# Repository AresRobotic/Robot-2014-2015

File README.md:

Robot-2014-2015
===============

Tous les documents, codes et cartes du robot de la coupe 2015

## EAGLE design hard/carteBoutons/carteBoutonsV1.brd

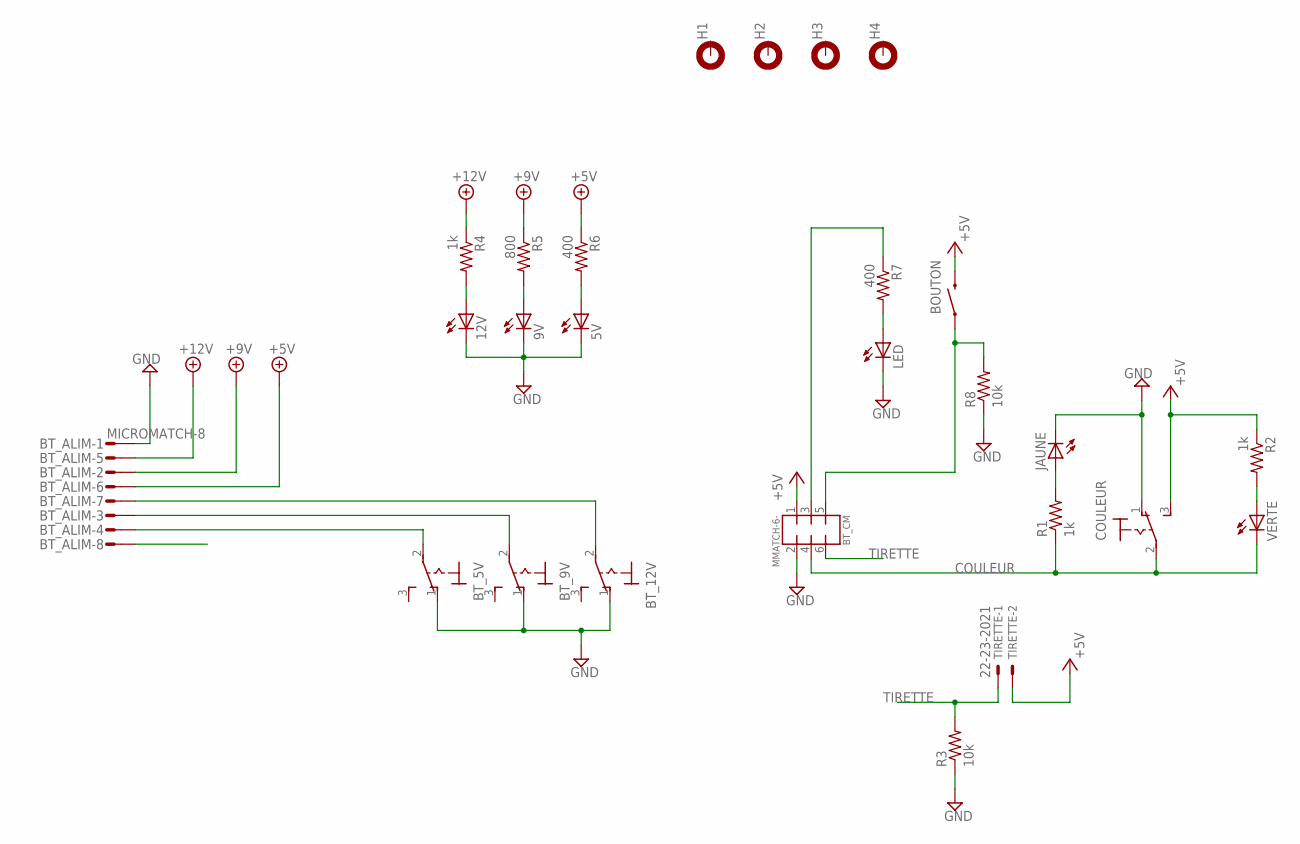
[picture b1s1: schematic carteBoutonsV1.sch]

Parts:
5V, 9V, 12V: LED3MM
BOUTON: SWITCH-MOMENTARY-2PTH; TACTILE-PTH
BT_5V, BT_9V, BT_12V: 320-916
BT_ALIM: MICROMATCH-8
BT_CM: MMATCH-6-; AMP-215079-6
COULEUR: 320-916
H1, H2, H3, H4: MOUNT-PAD-ROUND3.2; 3,2-PAD
JAUNE: LED3MM
LED: LED3MM
R1, R2, R4: 1k; 0805
R3, R8: 10k; 0805
R5: 800; 0805
R6, R7: 400; 0805
TIRETTE: 22-23-2021
VERTE: LED3MM

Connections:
+5V: BOUTON.3 (2), BT_ALIM.6, BT_CM.1 (3), COULEUR.3 (S), R2.1, R6.1, TIRETTE.2
+9V: BT_ALIM.2, R5.1
+12V: BT_ALIM.5, R4.1
COULEUR: BT_CM.4 (6), COULEUR.2, R1.1, VERTE.K (C)
GND: 5V.K (C), 9V.K (C), 12V.K (C), BT_5V.1 (O), BT_9V.1 (O), BT_12V.1 (O), BT_ALIM.1, BT_CM.2 (4), COULEUR.1 (O), JAUNE.K (C), LED.K (C), R3.1, R8.1
unnamed: R2.2, VERTE.A
unnamed: 12V.A, R4.2
unnamed: 9V.A, R5.2
unnamed: 5V.A, R6.2
unnamed: LED.A, R7.2
unnamed: BT_12V.2, BT_ALIM.7
unnamed: BT_9V.2, BT_ALIM.3
unnamed: BT_5V.2, BT_ALIM.4
unnamed: JAUNE.A, R1.2
unnamed: BT_CM.3 (5), R7.1
unnamed: BOUTON.1, BT_CM.5 (7), R8.2
TIRETTE: BT_CM.6 (8), R3.2, TIRETTE.1

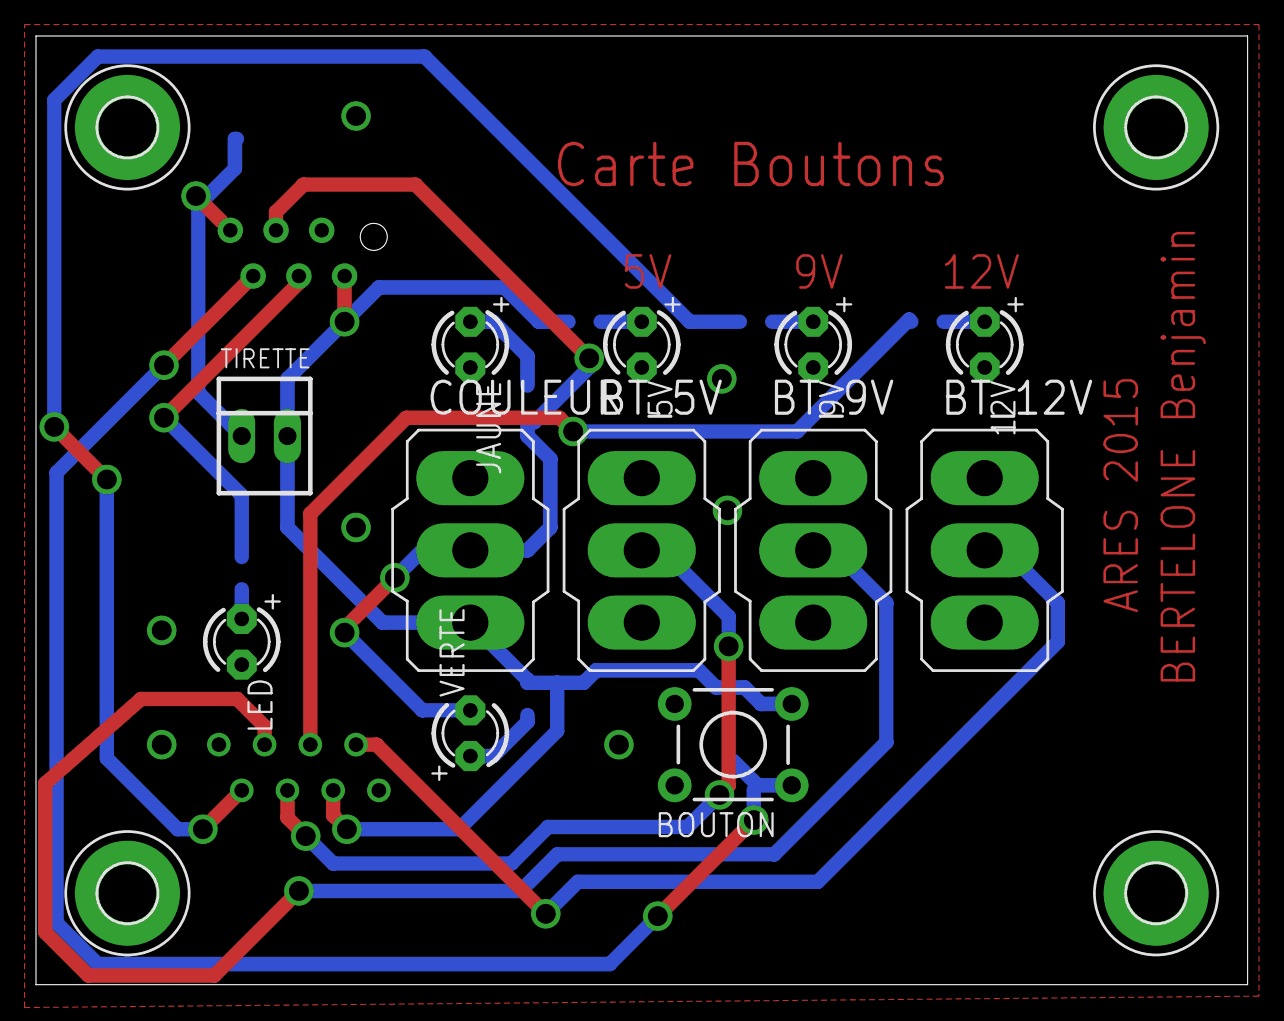
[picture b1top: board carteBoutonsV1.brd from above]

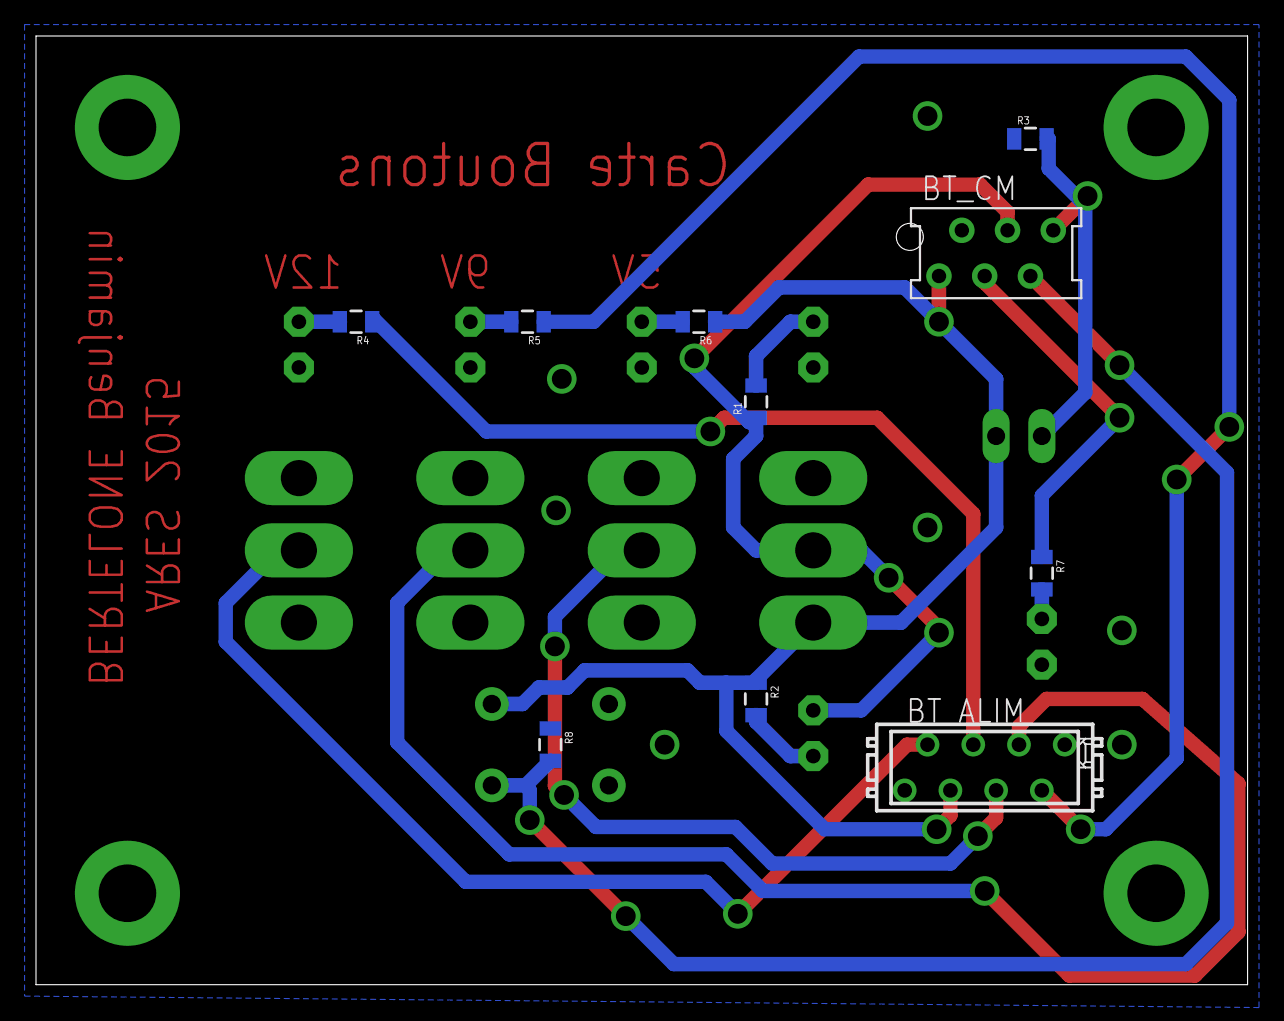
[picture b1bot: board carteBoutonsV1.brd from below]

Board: 2 copper layers, 67.3 x 52.7 mm, 26 parts (10 on the bottom side), 17 nets.

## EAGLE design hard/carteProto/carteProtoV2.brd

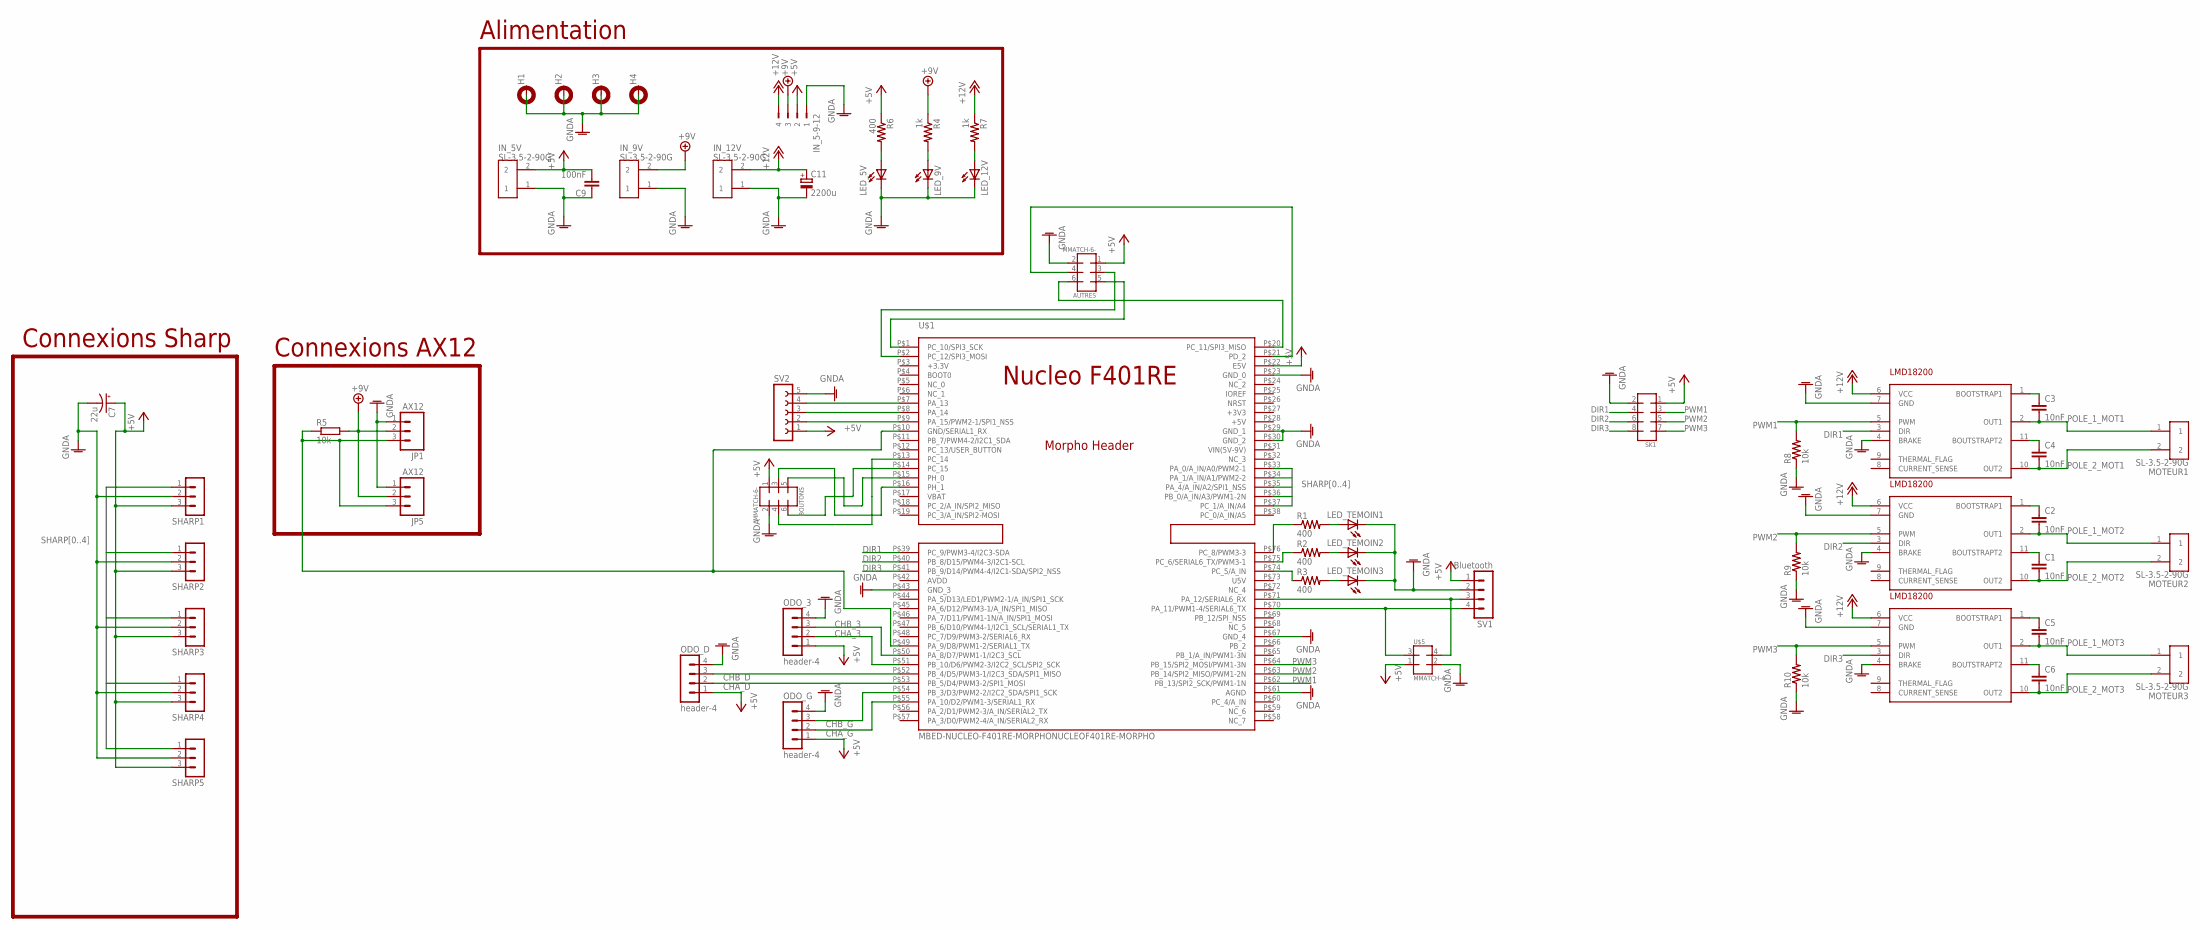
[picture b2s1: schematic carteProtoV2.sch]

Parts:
AUTRES: MMATCH-6-; AMP-215079-6
BOUTONS: MMATCH-6-; AMP-215079-6
C1, C2, C3, C4, C5, C6: 10nF; C0805
C7: 22u; CPOL-RADIAL-100UF-25V
C9: 100nF; C0805
C11: 2200u; TT5D11
H1, H2, H3, H4: MOUNT-PAD-ROUND3.2; 3,2-PAD
IN_5-9-12: 90G-4
IN_5V, IN_9V, IN_12V: SL-3.5-2-90G
JP1, JP5: AX12; MOLEX-1X3
LED_5V, LED_9V, LED_12V: LEDCHIPLED_0805; CHIPLED_0805
LED_TEMOIN1, LED_TEMOIN2, LED_TEMOIN3: LEDCHIPLED_0805; CHIPLED_0805
MOTEUR1, MOTEUR2, MOTEUR3: SL-3.5-2-90G
ODO_3: header-4; MA04-1
ODO_D: header-4; MA04-1
ODO_G: header-4; MA04-1
R1, R2, R3, R6: 400; 0805
R4, R7: 1k; 0805
R5: 10k; M0805
R8, R9, R10: 10k; 0805
SHARP1, SHARP2, SHARP3, SHARP4, SHARP5: MA03-1
SK1: MMATCH-8-PTH; AMP-215079-8
SV1: Bluetooth; MA04-1
SV2: FE05-1
U$1: MBED-NUCLEO-F401RE-MORPHONUCLEOF401RE-MORPHO; MORPHO-HEADERS
U$2, U$3, U$4: LMD18200
U$5: MMATCH-4-; AMP-215079-4

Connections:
+5V: AUTRES.1 (3), BOUTONS.1 (3), C7.1 (+), C9.2, IN_5-9-12.2, IN_5V.2, ODO_3.1, ODO_D.1, ODO_G.1, R6.1, SHARP1.3, SHARP2.3, SHARP3.3, SHARP4.3, SHARP5.3, SK1.1, SV1.1, SV2.1, U$1.P$22 (E5V), U$5.1 (5)
+9V: IN_5-9-12.3, IN_9V.2, JP1.2, JP5.2, R4.1, R5.2
+12V: C11.+, IN_5-9-12.4, IN_12V.2, R7.1, U$2.6 (VCC), U$3.6 (VCC), U$4.6 (VCC)
CHA_3: ODO_3.2, U$1.P$51 (PB_10/D6/PWM2-3/I2C2_SCL/SPI2_SCK)
CHA_D: ODO_D.2, U$1.P$53 (PB_5/D4/PWM3-2/SPI1_MOSI)
CHA_G: ODO_G.2, U$1.P$55 (PA_10/D2/PWM1-3/SERIAL1_RX)
CHB_3: ODO_3.3, U$1.P$50 (PA_8/D7/PWM1-1/I2C3_SCL)
CHB_D: ODO_D.3, U$1.P$52 (PB_4/D5/PWM3-1/I2C3_SDA/SPI1_MISO)
CHB_G: ODO_G.3, U$1.P$54 (PB_3/D3/PWM2-2/I2C2_SDA/SPI1_SCK)
DIR1: SK1.4, U$1.P$39 (PC_9/PWM3-4/I2C3-SDA), U$2.3 (DIR)
DIR2: SK1.6, U$1.P$40 (PB_8/D15/PWM4-3/I2C1-SCL), U$3.3 (DIR)
DIR3: SK1.8, U$1.P$41 (PB_9/D14/PWM4-4/I2C1-SDA/SPI2_NSS), U$4.3 (DIR)
GNDA: AUTRES.2 (4), BOUTONS.2 (4), C7.2 (-), C9.1, C11.-, H1.B3,2, H2.B3,2, H3.B3,2, H4.B3,2, IN_5-9-12.1, IN_5V.1, IN_9V.1, IN_12V.1, JP1.1, JP5.1, LED_5V.C, LED_9V.C, LED_12V.C, LED_TEMOIN1.C, LED_TEMOIN2.C, LED_TEMOIN3.C, ODO_3.4, ODO_D.4, ODO_G.4, R8.1, R9.1, R10.1, SHARP1.2, SHARP2.2, SHARP3.2, SHARP4.2, SHARP5.2, SK1.2, SV1.2, SV2.5, U$1.P$23 (GND_0), U$1.P$29 (GND_1), U$1.P$30 (GND_2), U$1.P$43 (GND_3), U$1.P$61 (AGND), U$1.P$67 (GND_4), U$2.4 (BRAKE), U$2.7 (GND), U$3.4 (BRAKE), U$3.7 (GND), U$4.4 (BRAKE), U$4.7 (GND), U$5.2 (6)
unnamed: C1.1, U$3.11 (BOUTSTRAPT2)
unnamed: C5.1, U$4.1 (BOOTSTRAP1)
unnamed: C2.1, U$3.1 (BOOTSTRAP1)
unnamed: C6.1, U$4.11 (BOUTSTRAPT2)
unnamed: C3.1, U$2.1 (BOOTSTRAP1)
unnamed: SV1.3, U$1.P$71 (PA_12/SERIAL6_RX), U$5.4 (8)
unnamed: C4.1, U$2.11 (BOUTSTRAPT2)
unnamed: SV1.4, U$1.P$70 (PA_11/PWM1-4/SERIAL6_TX), U$5.3 (7)
unnamed: LED_5V.A, R6.2
unnamed: LED_TEMOIN3.A, R3.2
unnamed: LED_12V.A, R7.2
unnamed: R1.1, U$1.P$76 (PC_8/PWM3-3)
unnamed: R2.1, U$1.P$75 (PC_6/SERIAL6_TX/PWM3-1)
unnamed: R3.1, U$1.P$74 (PC_5/A_IN)
unnamed: LED_TEMOIN1.A, R1.2
unnamed: LED_TEMOIN2.A, R2.2
unnamed: BOUTONS.3 (5), U$1.P$16 (PH_1)
unnamed: BOUTONS.5 (7), U$1.P$15 (PH_0)
unnamed: BOUTONS.6 (8), U$1.P$14 (PC_15)
unnamed: BOUTONS.4 (6), U$1.P$13 (PC_14)
unnamed: SV2.4, U$1.P$7 (PA_13)
unnamed: SV2.3, U$1.P$8 (PA_14)
unnamed: SV2.2, U$1.P$9 (PA_15/PWM2-1/SPI1_NSS)
unnamed: AUTRES.3 (5), U$1.P$2 (PC_12/SPI3_MOSI)
unnamed: LED_9V.A, R4.2
unnamed: AUTRES.5 (7), U$1.P$1 (PC_10/SPI3_SCK)
unnamed: AUTRES.4 (6), U$1.P$21 (PD_2)
unnamed: AUTRES.6 (8), U$1.P$20 (PC_11/SPI3_MISO)
POLE_1_MOT1: C3.2, MOTEUR1.1, U$2.2 (OUT1)
POLE_1_MOT2: C2.2, MOTEUR2.1, U$3.2 (OUT1)
POLE_1_MOT3: C5.2, MOTEUR3.1, U$4.2 (OUT1)
POLE_2_MOT1: C4.2, MOTEUR1.2, U$2.10 (OUT2)
POLE_2_MOT2: C1.2, MOTEUR2.2, U$3.10 (OUT2)
POLE_2_MOT3: C6.2, MOTEUR3.2, U$4.10 (OUT2)
PWM1: R8.2, SK1.3, U$1.P$62 (PB_13/SPI2_SCK/PWM1-1N), U$2.5 (PWM)
PWM2: R9.2, SK1.5, U$1.P$63 (PB_14/SPI2_MISO/PWM1-2N), U$3.5 (PWM)
PWM3: R10.2, SK1.7, U$1.P$64 (PB_15/SPI2_MOSI/PWM1-3N), U$4.5 (PWM)
SERIAL1: JP1.3, JP5.3, R5.1, U$1.P$10 (GND/SERIAL1_RX), U$1.P$49 (PA_9/D8/PWM1-2/SERIAL1_TX)
SHARP0: SHARP1.1, U$1.P$33 (PA_0/A_IN/A0/PWM2-1)
SHARP1: SHARP2.1, U$1.P$34 (PA_1/A_IN/A1/PWM2-2)
SHARP2: SHARP3.1, U$1.P$35 (PA_4/A_IN/A2/SPI1_NSS)
SHARP3: SHARP4.1, U$1.P$36 (PB_0/A_IN/A3/PWM1-2N)
SHARP4: SHARP5.1, U$1.P$37 (PC_1/A_IN/A4)

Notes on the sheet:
Connexions Sharp
Connexions AX12
Alimentation

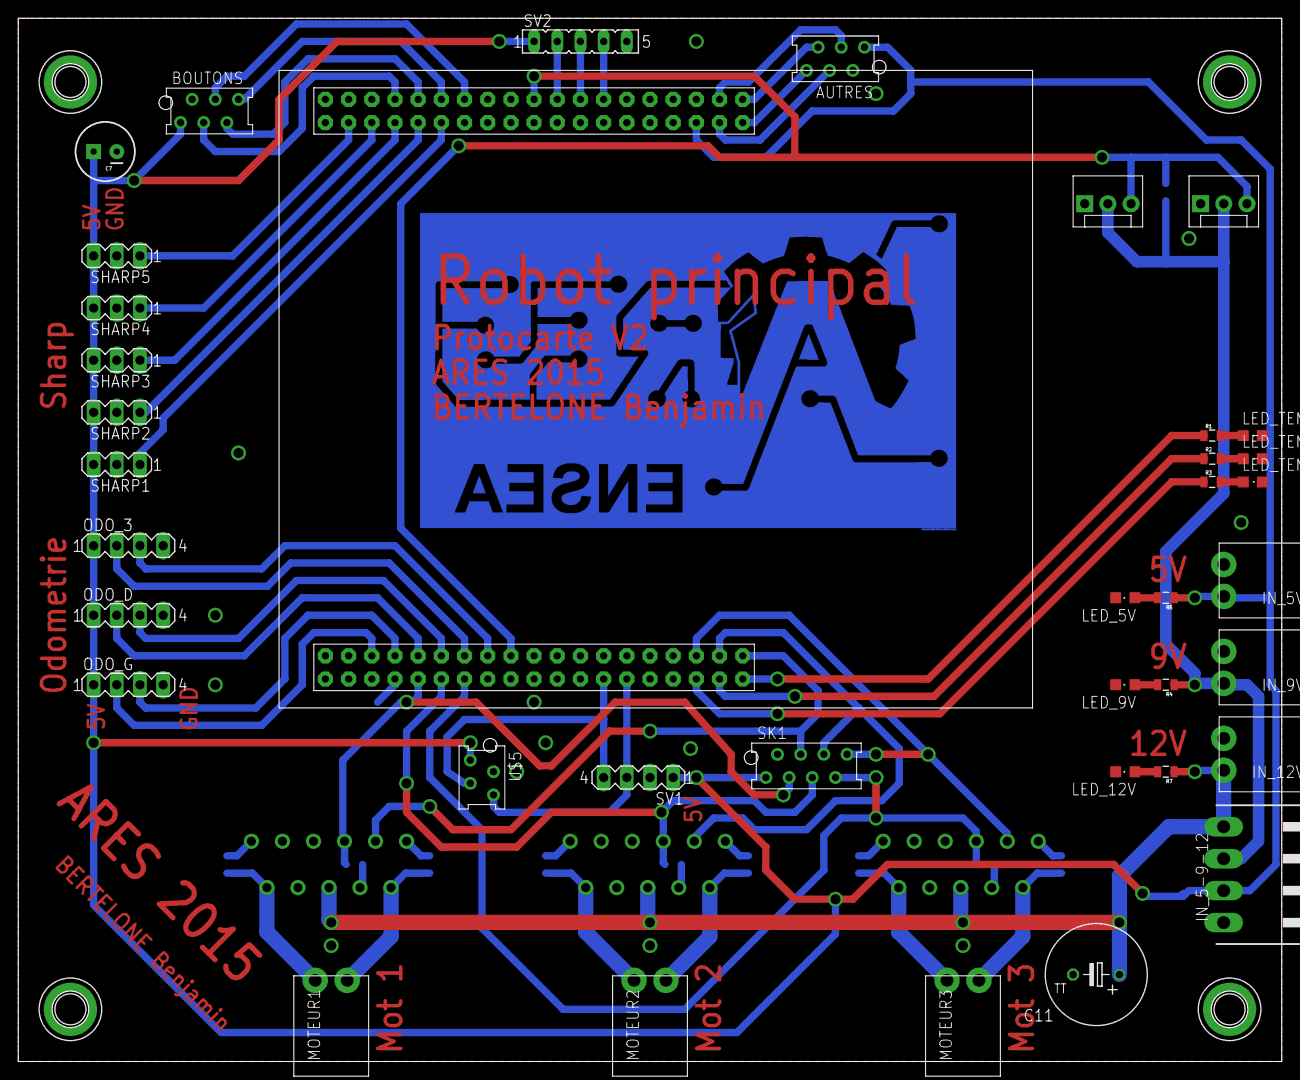
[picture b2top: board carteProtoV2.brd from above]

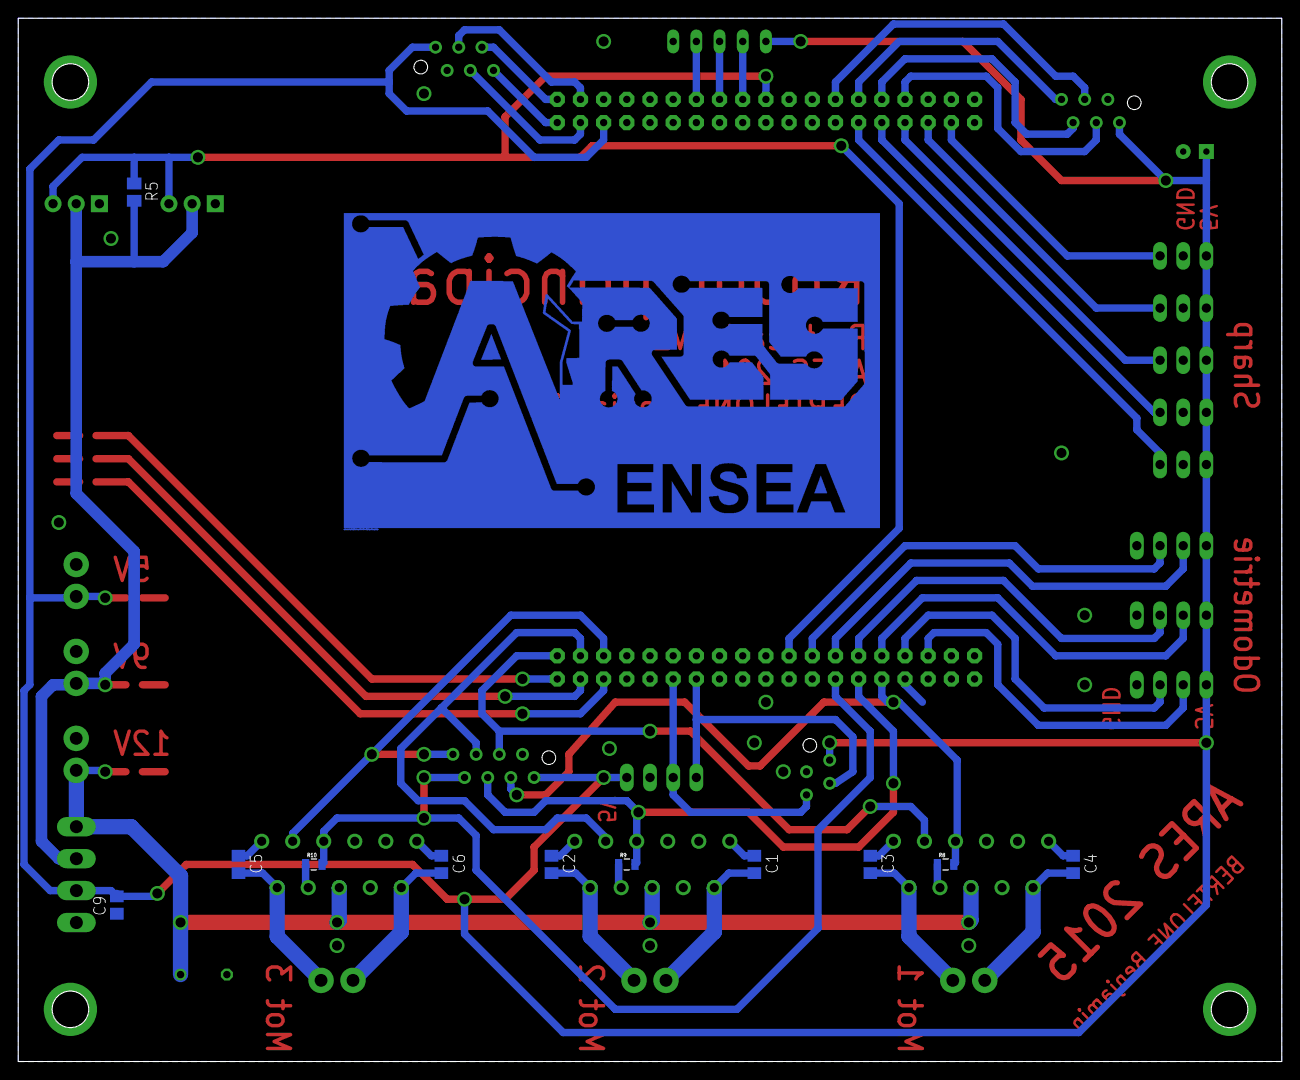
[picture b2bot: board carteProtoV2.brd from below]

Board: 2 copper layers, 138.4 x 114.3 mm, 56 parts (11 on the bottom side), 56 nets.

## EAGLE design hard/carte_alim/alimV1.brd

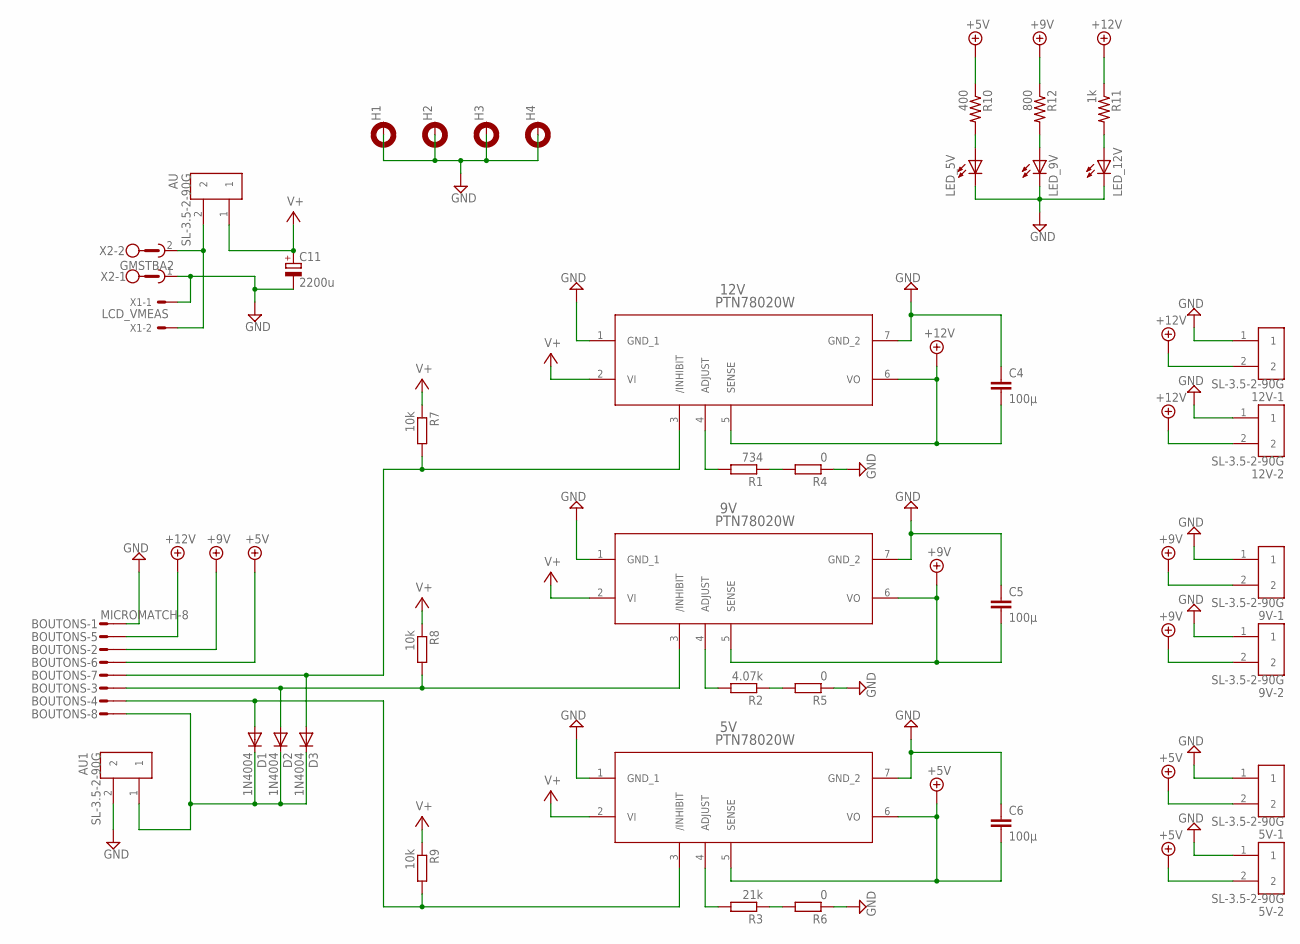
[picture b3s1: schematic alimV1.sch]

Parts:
5V, 9V, 12V: PTN78020W; EUK7
5V-1, 5V-2, 9V-1, 9V-2, 12V-1, 12V-2: SL-3.5-2-90G
AU, AU1: SL-3.5-2-90G
BOUTONS: MICROMATCH-8
C4, C5, C6: 100µ; C025-025X050
C11: 2200u; TT5D11
D1, D2, D3: 1N4004; DO41-10
H1, H2, H3, H4: MOUNT-PAD-ROUND3.2; 3,2-PAD
LED_5V, LED_9V, LED_12V: LEDCHIPLED_0805; CHIPLED_0805
R1: 734; R0805
R2: 4.07k; R0805
R3: 21k; R0805
R4, R5, R6: 0; R0805
R7, R8, R9: 10k; R0805
R10: 400; 0805
R11: 1k; 0805
R12: 800; 0805
X1: LCD_VMEAS; 22-23-2021
X2: GMSTBA2

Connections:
+5V: 5V.5 (SENSE), 5V.6 (VO), 5V-1.2, 5V-2.2, BOUTONS.6, C6.2, R10.1
+9V: 9V.5 (SENSE), 9V.6 (VO), 9V-1.2, 9V-2.2, BOUTONS.2, C5.2, R12.1
+12V: 12V.5 (SENSE), 12V.6 (VO), 12V-1.2, 12V-2.2, BOUTONS.5, C4.2, R11.1
GND: 5V.1 (GND_1), 5V.7 (GND_2), 5V-1.1, 5V-2.1, 9V.1 (GND_1), 9V.7 (GND_2), 9V-1.1, 9V-2.1, 12V.1 (GND_1), 12V.7 (GND_2), 12V-1.1, 12V-2.1, AU1.2, BOUTONS.1, C4.1, C5.1, C6.1, C11.-, H1.B3,2, H2.B3,2, H3.B3,2, H4.B3,2, LED_5V.C, LED_9V.C, LED_12V.C, R4.1, R5.1, R6.1, X1.1, X2.1
unnamed: R3.1, R6.2
unnamed: 12V.4 (ADJUST), R1.2
unnamed: 9V.4 (ADJUST), R2.2
unnamed: 5V.4 (ADJUST), R3.2
unnamed: R2.1, R5.2
unnamed: R1.1, R4.2
unnamed: 12V.3 (/INHIBIT), BOUTONS.7, D3.A, R7.2
unnamed: 9V.3 (/INHIBIT), BOUTONS.3, D2.A, R8.2
unnamed: 5V.3 (/INHIBIT), BOUTONS.4, D1.A, R9.2
unnamed: AU1.1, BOUTONS.8, D1.C, D2.C, D3.C
unnamed: AU.2, X1.2, X2.2
unnamed: LED_5V.A, R10.2
unnamed: LED_12V.A, R11.2
unnamed: LED_9V.A, R12.2
V+: 5V.2 (VI), 9V.2 (VI), 12V.2 (VI), AU.1, C11.+, R7.1, R8.1, R9.1

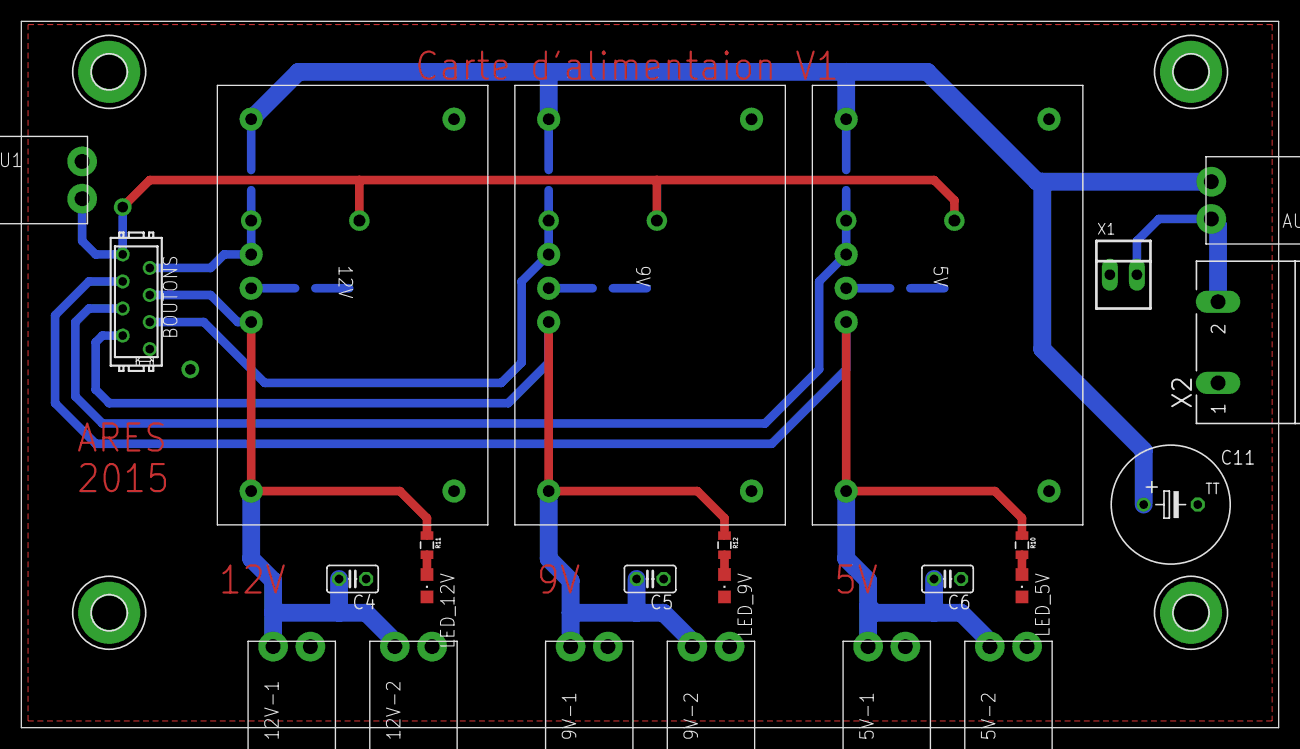
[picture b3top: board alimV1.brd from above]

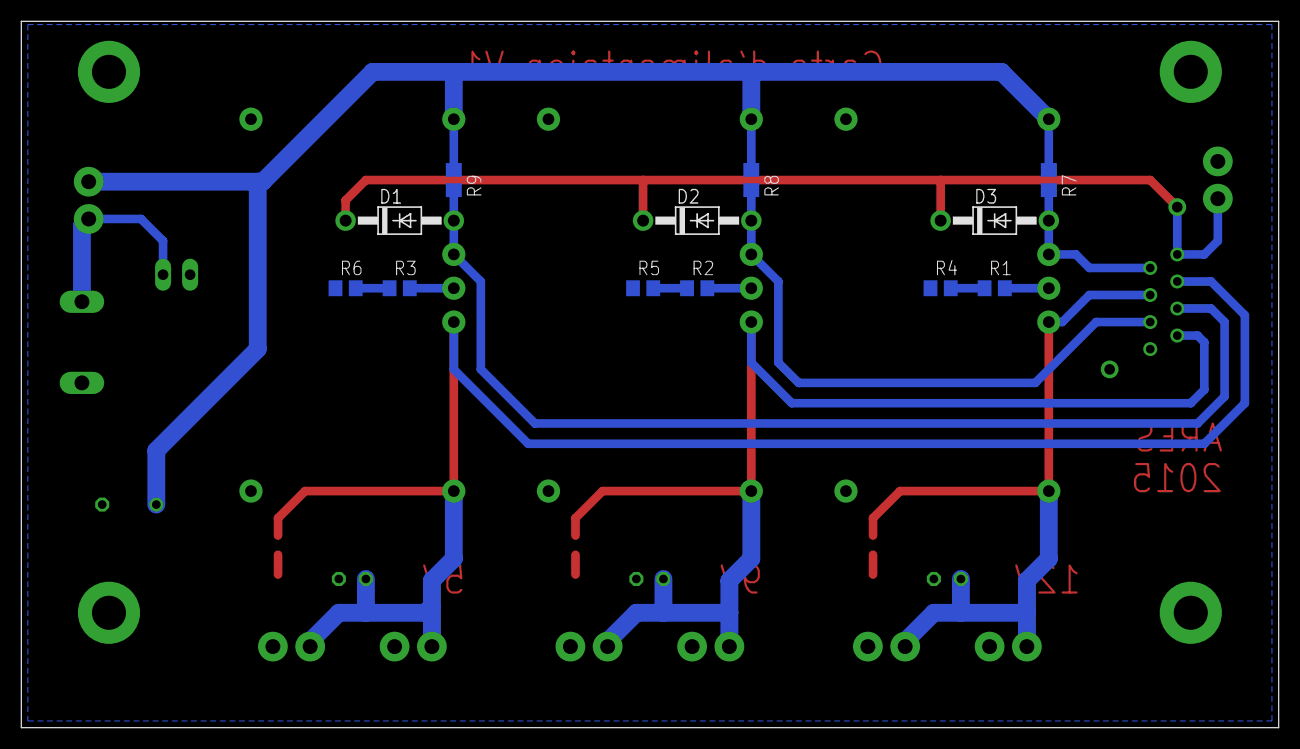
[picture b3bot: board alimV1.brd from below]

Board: 2 copper layers, 118.1 x 66.3 mm, 40 parts (12 on the bottom side), 19 nets.

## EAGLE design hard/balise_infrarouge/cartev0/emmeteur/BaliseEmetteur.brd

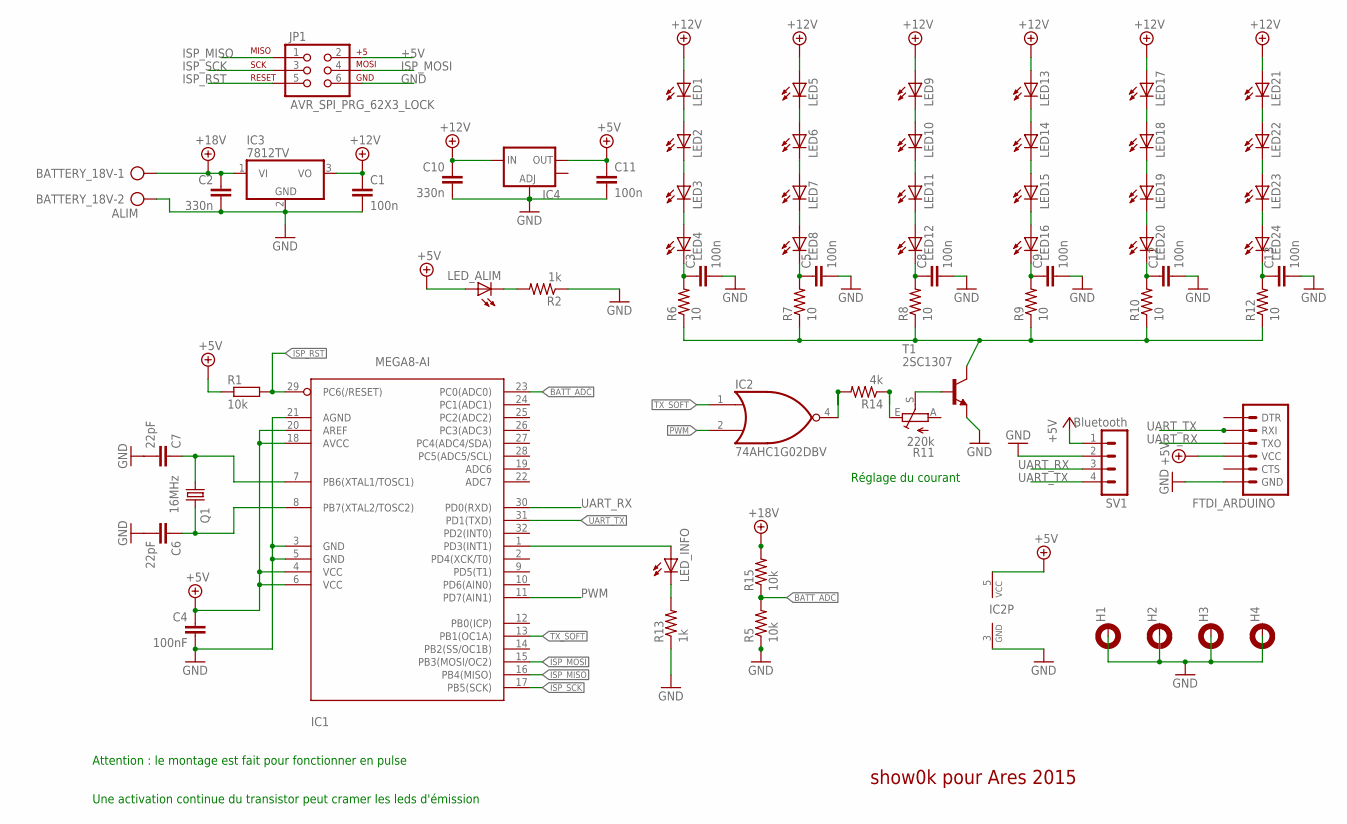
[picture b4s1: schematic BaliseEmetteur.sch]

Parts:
BATTERY_18V: ALIM; AK500/2
C1, C3, C5, C8, C9, C11, C12, C13: 100n; C0805
C2, C10: 330n; C0805
C4: 100nF; C0805
C6, C7: 22pF; C0805
FTDI_ARDUINO: ARDUINO_SERIAL_PROGRAMPTH; 1X06
H1, H2, H3, H4: MOUNT-PAD-ROUND3.2; 3,2-PAD
IC1: MEGA8-AI; TQFP32-08
IC2: 74AHC1G02DBV; SOT23-5
IC3: 7812TV; TO220V
IC4: V_REG_LM1117SOT223; SOT223
JP1: AVR_SPI_PRG_62X3_LOCK; 2X3_LOCK
LED1, LED2, LED3, LED4, LED5, LED6, LED7, LED8, LED9, LED10, LED11, LED12, LED13, LED14, LED15, LED16, LED17, LED18, LED19, LED20, LED21, LED22, LED23, LED24: LEDB155; Q62902-B155
LED_ALIM: LEDCHIPLED_0805; CHIPLED_0805
LED_INFO: LEDCHIPLED_0805; CHIPLED_0805
Q1: 16MHz; HC49/S
R1: 10k; 0207/2V
R2, R13: 1k; M0805
R5, R15: 10k; M0805
R6, R7, R8, R9, R10, R12: 10; M0805
R11: 220k; CA9V
R14: 4k; M0805
SV1: Bluetooth; MA04-1
T1: 2SC1307; TO220AV

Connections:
+5V: C4.1, C11.1, FTDI_ARDUINO.4 (VCC), IC1.4 (VCC), IC1.6 (VCC), IC1.18 (AVCC), IC1.20 (AREF), IC2.5 (VCC), IC4.2 (OUT), JP1.2, LED_ALIM.A, R1.1, SV1.1
+12V: C1.1, C10.1, IC3.3 (VO), IC4.3 (IN), LED1.A, LED5.A, LED9.A, LED13.A, LED17.A, LED21.A
+18V: BATTERY_18V.1, C2.1, IC3.1 (VI), R15.2
BATT_ADC: IC1.23 (PC0(ADC0)), R5.2, R15.1
GND: BATTERY_18V.2, C1.2, C2.2, C3.2, C4.2, C5.2, C6.2, C7.2, C8.2, C9.2, C10.2, C11.2, C12.2, C13.2, FTDI_ARDUINO.6 (GND), H1.B3,2, H2.B3,2, H3.B3,2, H4.B3,2, IC1.3 (GND), IC1.5 (GND), IC1.21 (AGND), IC2.3 (GND), IC3.2 (GND), IC4.1 (ADJ), JP1.6, R2.1, R5.1, R13.1, SV1.2, T1.3 (E)
ISP_MISO: IC1.16 (PB4(MISO)), JP1.1
ISP_MOSI: IC1.15 (PB3(MOSI/OC2)), JP1.4
ISP_RST: IC1.29 (PC6(/RESET)), JP1.5, R1.2
ISP_SCK: IC1.17 (PB5(SCK)), JP1.3
unnamed: LED_INFO.C, R13.2
unnamed: LED1.K (C), LED2.A
unnamed: IC2.4 (O), R14.2
unnamed: IC1.1 (PD3(INT1)), LED_INFO.A
unnamed: LED3.K (C), LED4.A
unnamed: LED6.K (C), LED7.A
unnamed: LED5.K (C), LED6.A
unnamed: C7.1, IC1.7 (PB6(XTAL1/TOSC1)), Q1.1
unnamed: C6.1, IC1.8 (PB7(XTAL2/TOSC2)), Q1.2
unnamed: LED7.K (C), LED8.A
unnamed: LED18.K (C), LED19.A
unnamed: LED9.K (C), LED10.A
unnamed: LED2.K (C), LED3.A
unnamed: LED11.K (C), LED12.A
unnamed: R11.E, R14.1
unnamed: LED13.K (C), LED14.A
unnamed: R6.1, R7.1, R8.1, R9.1, R10.1, R12.1, T1.2 (C)
unnamed: LED15.K (C), LED16.A
unnamed: LED22.K (C), LED23.A
unnamed: LED17.K (C), LED18.A
unnamed: LED19.K (C), LED20.A
unnamed: C3.1, LED4.K (C), R6.2
unnamed: LED21.K (C), LED22.A
unnamed: LED10.K (C), LED11.A
unnamed: LED23.K (C), LED24.A
unnamed: C5.1, LED8.K (C), R7.2
unnamed: LED14.K (C), LED15.A
unnamed: C8.1, LED12.K (C), R8.2
unnamed: C9.1, LED16.K (C), R9.2
unnamed: C12.1, LED20.K (C), R10.2
unnamed: C13.1, LED24.K (C), R12.2
unnamed: LED_ALIM.C, R2.2
PWM: IC1.11 (PD7(AIN1)), IC2.2 (I1)
TIP122: R11.S, T1.1 (B)
TX_SOFT: IC1.13 (PB1(OC1A)), IC2.1 (I0)
UART_RX: FTDI_ARDUINO.3 (TXO), IC1.30 (PD0(RXD)), SV1.3
UART_TX: FTDI_ARDUINO.2 (RXI), IC1.31 (PD1(TXD)), SV1.4

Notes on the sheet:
Réglage du courant
Attention : le montage est fait pour fonctionner en pulse
Une activation continue du transistor peut cramer les leds d'émission
show0k pour Ares 2015

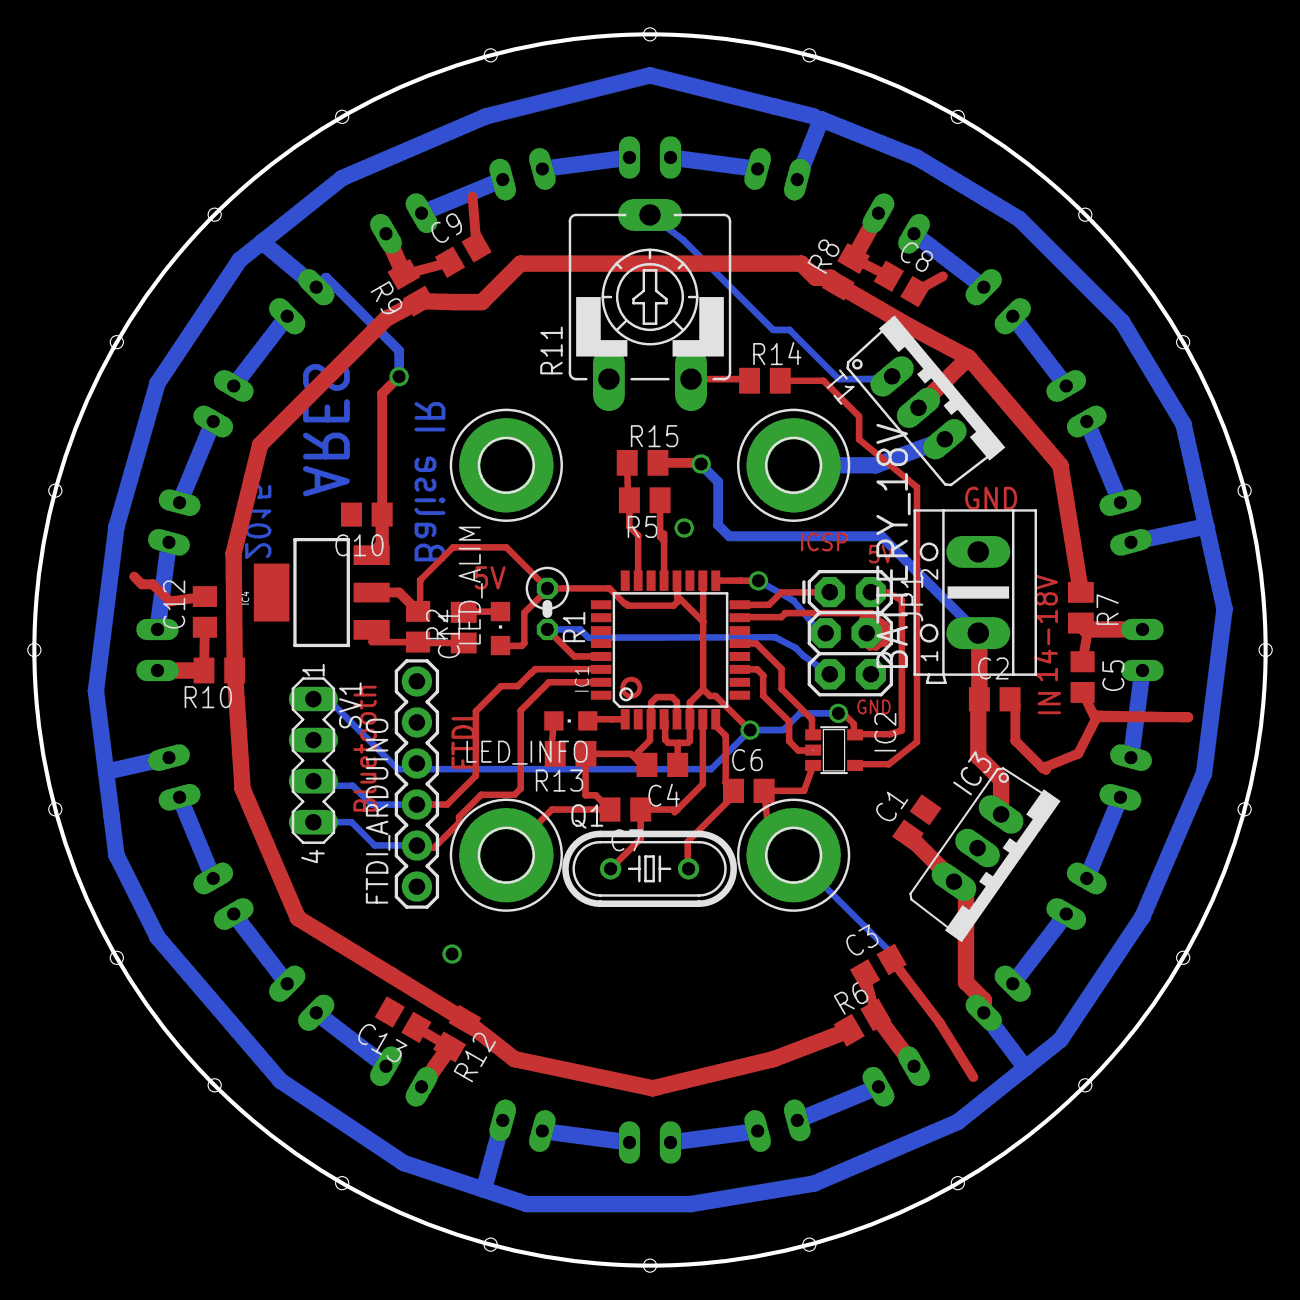
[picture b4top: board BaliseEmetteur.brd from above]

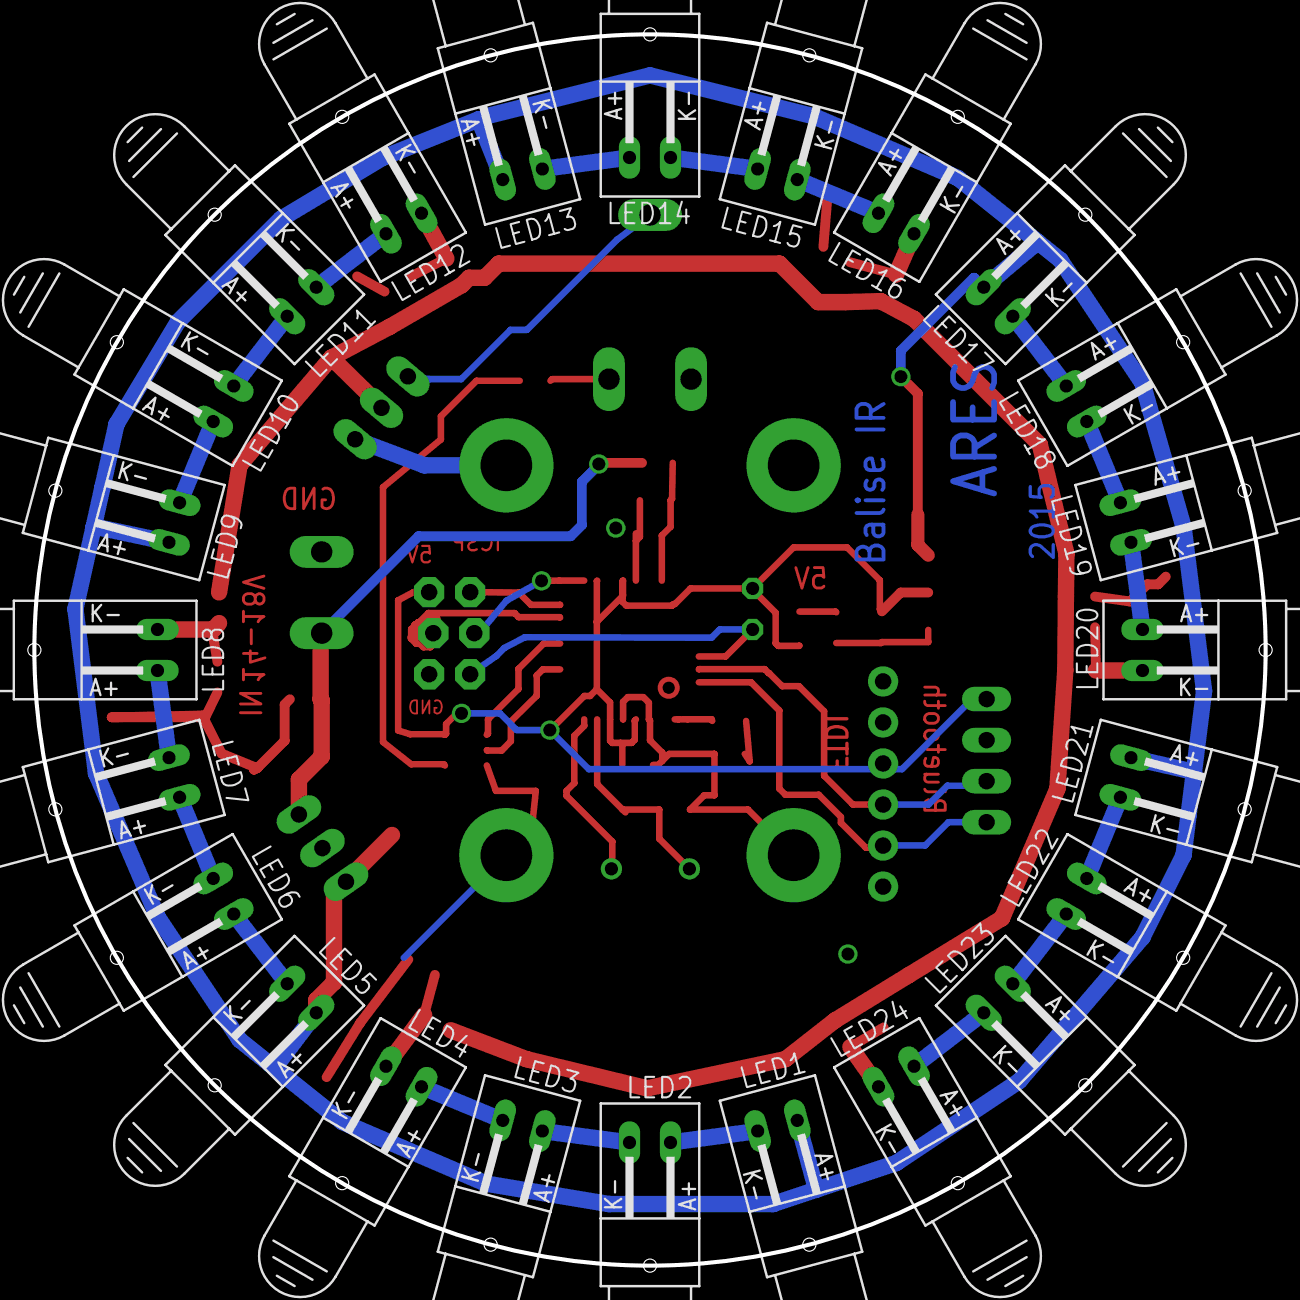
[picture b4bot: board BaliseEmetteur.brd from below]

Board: 2 copper layers, 76.2 x 76.2 mm, 66 parts (24 on the bottom side), 46 nets.

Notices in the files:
parts and their libraries:
SparkFun-Passives: Licensing: CC v3.0 Share-Alike You are welcome to use this library for commercial purposes.
SparkFun-PowerIC: Licensing: Creative Commons ShareAlike 4.0 International - https://creativecommons.org/licenses/by-sa/4.0
